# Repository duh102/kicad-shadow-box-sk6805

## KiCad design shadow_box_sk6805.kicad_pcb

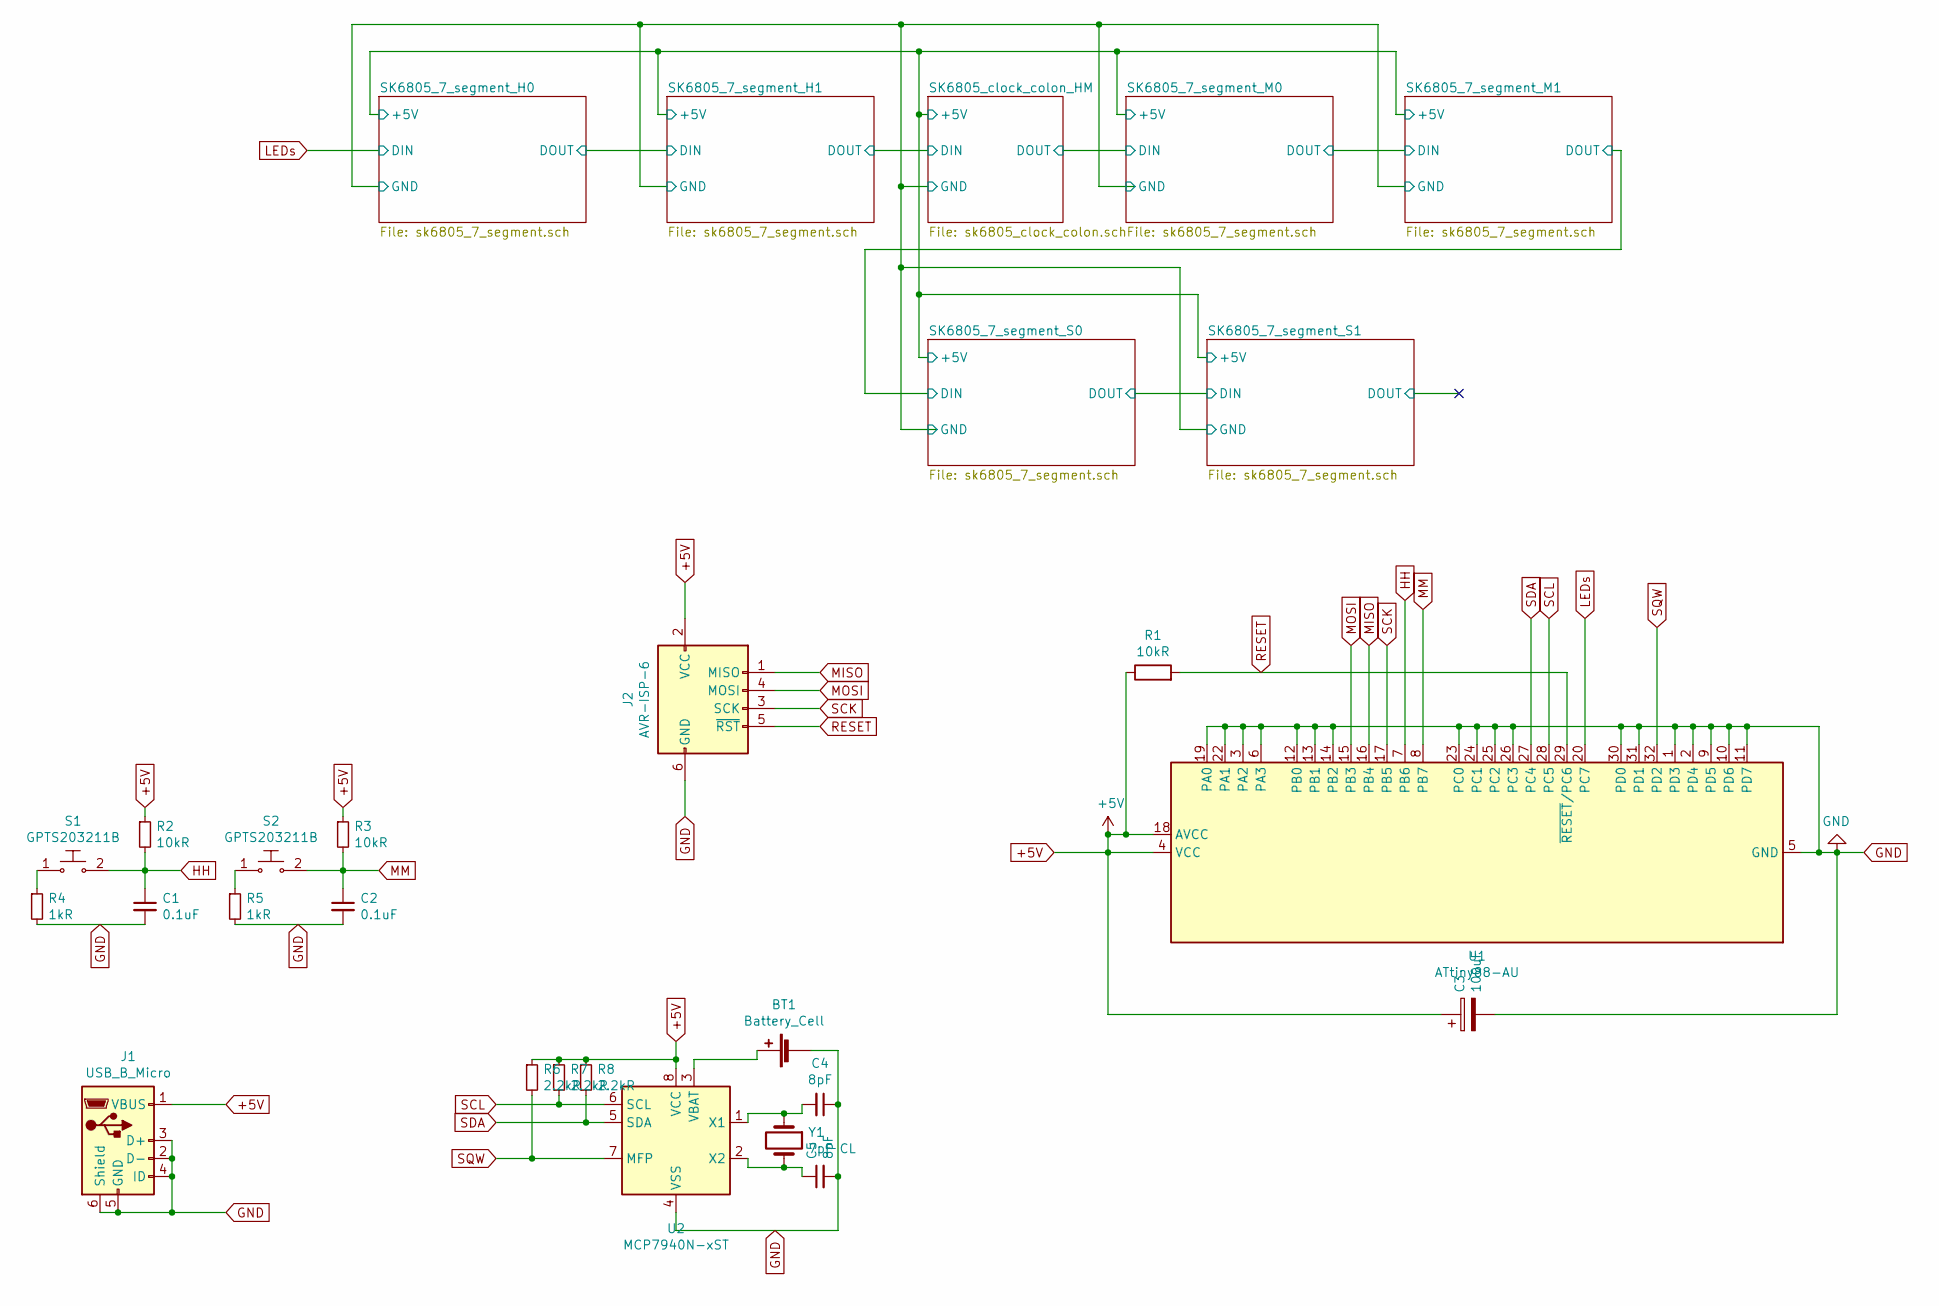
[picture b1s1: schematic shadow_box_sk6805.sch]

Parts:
BT1: Battery_Cell; BatteryHolder_Keystone_3034_1x20mm
C1, C2: 0.1uF; C_0805_2012Metric
C3: 100uF; CP_Radial_D6.3mm_P2.50mm
C4, C5: 8pF; C_0805_2012Metric
J1: USB_B_Micro; USB_Micro_B_Female_10118194-0001LF
J2: AVR-ISP-6; PinHeader_2x03_P2.54mm_Vertical_SMD
R1, R2, R3: 10kR; R_0805_2012Metric
R4, R5: 1kR; R_0805_2012Metric
R6, R7, R8: 2.2kR; R_0805_2012Metric
S1, S2: GPTS203211B; SW_SPST_FSMSM; MPN GPTS203211B; Digi-Key_PN CW181-ND
U1: ATtiny88-AU; TQFP-32_7x7mm_P0.8mm
U2: MCP7940N-xST; SOIC-8_3.9x4.9mm_P1.27mm
Y1: 7pF CL; Crystal_SMD_3215-2Pin_3.2x1.5mm

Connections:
+5V: C3.1, J1.1 (VBUS), J2.2 (VCC), R1.1, R2.1, R3.1, R6.1, R7.1, R8.1, U1.4 (VCC), U1.18 (AVCC), U2.8 (VCC); also elsewhere on the board
GND: BT1.2 (-), C1.2, C2.2, C3.2, C4.1, C5.2, J1.2 (D-), J1.3 (D+), J1.4 (ID), J1.5 (GND), J1.6 (Shield), J2.6 (GND), R4.2, R5.2, U1.1 (PD3), U1.2 (PD4), U1.3 (PA2), U1.5 (GND), U1.6 (PA3), U1.9 (PD5), U1.10 (PD6), U1.11 (PD7), U1.12 (PB0), U1.13 (PB1), U1.14 (PB2), U1.19 (PA0), U1.21 (GND), U1.22 (PA1), U1.23 (PC0), U1.24 (PC1), U1.25 (PC2), U1.26 (PC3), U1.30 (PD0), U1.31 (PD1), U2.4 (VSS); also elsewhere on the board
HH: C1.1, R2.2, S1.2, U1.7 (PB6)
LEDs: U1.20 (PC7); also elsewhere on the board
MISO: J2.1 (MISO), U1.16 (PB4)
MM: C2.1, R3.2, S2.2, U1.8 (PB7)
MOSI: J2.4 (MOSI), U1.15 (PB3)
unnamed: BT1.1 (+), U2.3 (VBAT)
unnamed: C4.2, U2.1 (X1), Y1.1
unnamed: C5.1, U2.2 (X2), Y1.2
unnamed: R4.1, S1.1
unnamed: R5.1, S2.1
RESET: J2.5 (~RST), R1.2, U1.29 (~RESET~/PC6)
SCK: J2.3 (SCK), U1.17 (PB5)
SCL: R7.2, U1.28 (PC5), U2.6 (SCL)
SDA: R8.2, U1.27 (PC4), U2.5 (SDA)
SQW: R6.2, U1.32 (PD2), U2.7 (MFP)

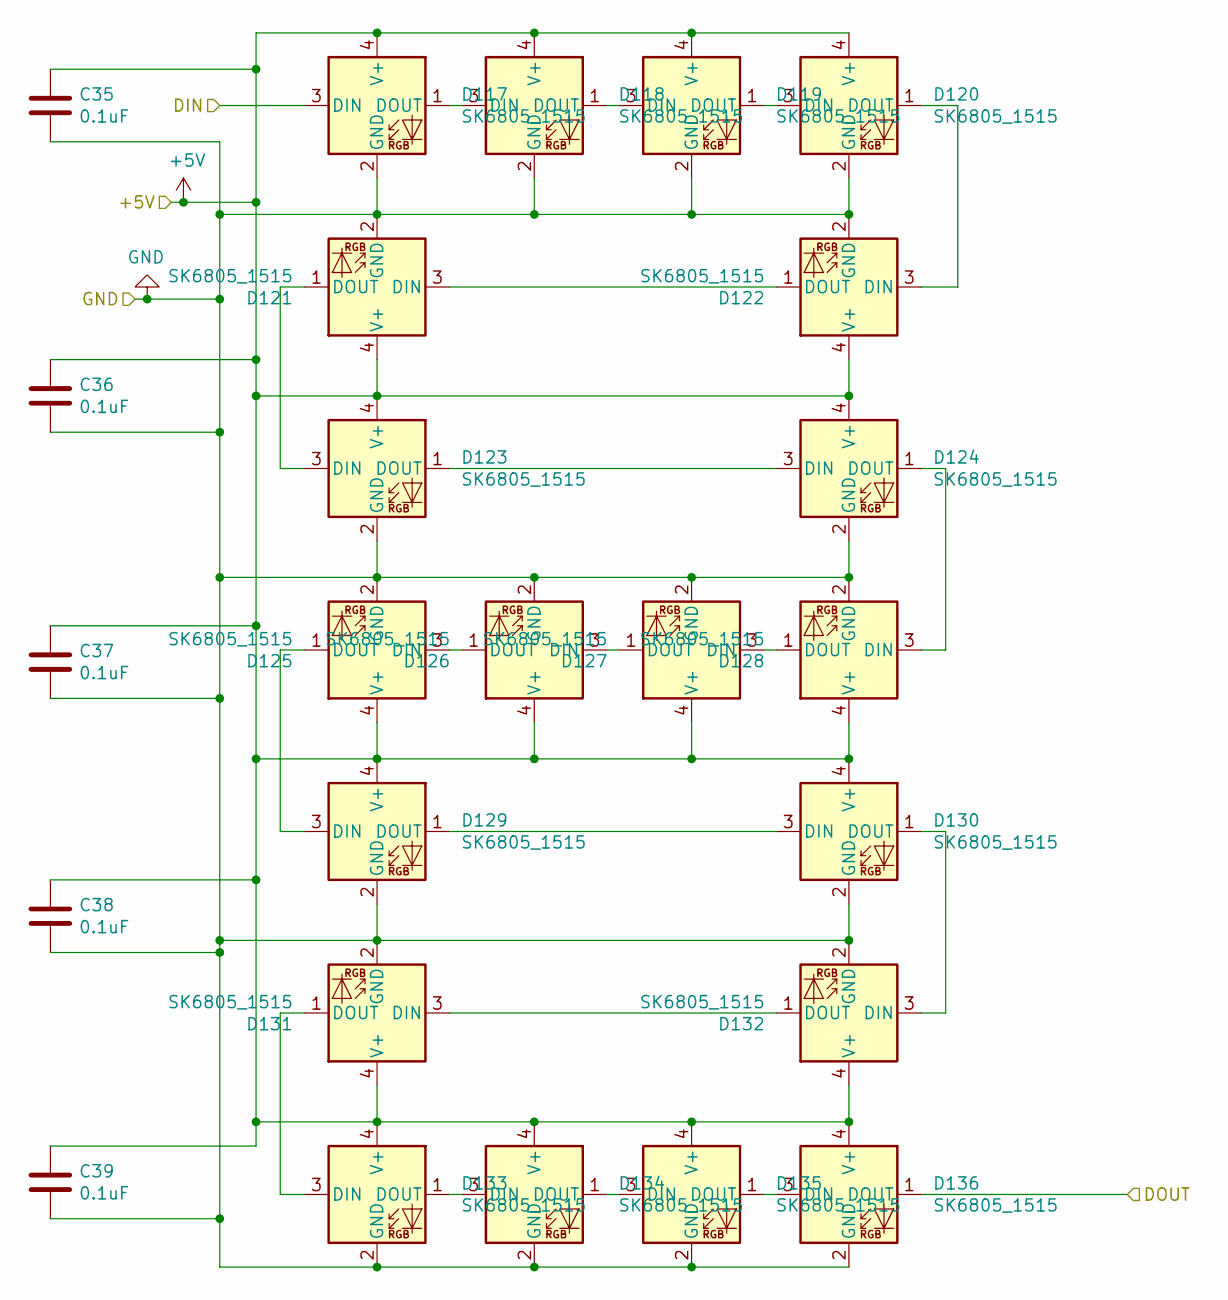
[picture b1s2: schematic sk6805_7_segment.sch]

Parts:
C35, C36, C37, C38, C39: 0.1uF; C_0805_2012Metric
D117, D118, D119, D120, D121, D122, D123, D124, D125, D126, D127, D128, D129, D130, D131, D132, D133, D134, D135, D136: SK6805_1515; LED_SK6805_PLCC4_1.5x1.5mm_P0.65mm

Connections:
+5V: C35.1, C36.1, C37.1, C38.1, C39.1, D117.4 (V+), D118.4 (V+), D119.4 (V+), D120.4 (V+), D121.4 (V+), D122.4 (V+), D123.4 (V+), D124.4 (V+), D125.4 (V+), D126.4 (V+), D127.4 (V+), D128.4 (V+), D129.4 (V+), D130.4 (V+), D131.4 (V+), D132.4 (V+), D133.4 (V+), D134.4 (V+), D135.4 (V+), D136.4 (V+); also elsewhere on the board
/SK6805_7_segment_H1/DIN: D136.1 (DOUT); also elsewhere on the board
GND: C35.2, C36.2, C37.2, C38.2, C39.2, D117.2 (GND), D118.2 (GND), D119.2 (GND), D120.2 (GND), D121.2 (GND), D122.2 (GND), D123.2 (GND), D124.2 (GND), D125.2 (GND), D126.2 (GND), D127.2 (GND), D128.2 (GND), D129.2 (GND), D130.2 (GND), D131.2 (GND), D132.2 (GND), D133.2 (GND), D134.2 (GND), D135.2 (GND), D136.2 (GND); also elsewhere on the board
LEDs: D117.3 (DIN); also elsewhere on the board
unnamed: D117.1 (DOUT), D118.3 (DIN)
unnamed: D118.1 (DOUT), D119.3 (DIN)
unnamed: D119.1 (DOUT), D120.3 (DIN)
unnamed: D120.1 (DOUT), D122.3 (DIN)
unnamed: D121.1 (DOUT), D123.3 (DIN)
unnamed: D121.3 (DIN), D122.1 (DOUT)
unnamed: D123.1 (DOUT), D124.3 (DIN)
unnamed: D124.1 (DOUT), D128.3 (DIN)
unnamed: D125.1 (DOUT), D129.3 (DIN)
unnamed: D125.3 (DIN), D126.1 (DOUT)
unnamed: D126.3 (DIN), D127.1 (DOUT)
unnamed: D127.3 (DIN), D128.1 (DOUT)
unnamed: D129.1 (DOUT), D130.3 (DIN)
unnamed: D130.1 (DOUT), D132.3 (DIN)
unnamed: D131.1 (DOUT), D133.3 (DIN)
unnamed: D131.3 (DIN), D132.1 (DOUT)
unnamed: D133.1 (DOUT), D134.3 (DIN)
unnamed: D134.1 (DOUT), D135.3 (DIN)
unnamed: D135.1 (DOUT), D136.3 (DIN)

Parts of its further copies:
C6, C7, C8, C9, C10, C11, C12, C13, C14, C15, C20, C21, C22, C23, C24, C25, C26, C27, C28, C29, C30, C31, C32, C33, C34: 0.1uF; C_0805_2012Metric
D1, D2, D3, D4, D5, D6, D7, D8, D9, D10, D11, D12, D13, D14, D15, D16, D17, D18, D19, D20, D21, D22, D23, D24, D25, D26, D27, D28, D29, D30, D31, D32, D33, D34, D35, D36, D37, D38, D39, D40, D57, D58, D59, D60, D61, D62, D63, D64, D65, D66, D67, D68, D69, D70, D71, D72, D73, D74, D75, D76, D77, D78, D79, D80, D81, D82, D83, D84, D85, D86, D87, D88, D89, D90, D91, D92, D93, D94, D95, D96, D97, D98, D99, D100, D101, D102, D103, D104, D105, D106, D107, D108, D109, D110, D111, D112, D113, D114, D115, D116: SK6805_1515; LED_SK6805_PLCC4_1.5x1.5mm_P0.65mm

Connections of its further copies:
+5V: C6.1, C7.1, C8.1, C9.1, C10.1, C11.1, C12.1, C13.1, C14.1, C15.1, C20.1, C21.1, C22.1, C23.1, C24.1, C25.1, C26.1, C27.1, C28.1, C29.1, C30.1, C31.1, C32.1, C33.1, C34.1, D1.4 (V+), D2.4 (V+), D3.4 (V+), D4.4 (V+), D5.4 (V+), D6.4 (V+), D7.4 (V+), D8.4 (V+), D9.4 (V+), D10.4 (V+), D11.4 (V+), D12.4 (V+), D13.4 (V+), D14.4 (V+), D15.4 (V+), D16.4 (V+), D17.4 (V+), D18.4 (V+), D19.4 (V+), D20.4 (V+), D21.4 (V+), D22.4 (V+), D23.4 (V+), D24.4 (V+), D25.4 (V+), D26.4 (V+), D27.4 (V+), D28.4 (V+), D29.4 (V+), D30.4 (V+), D31.4 (V+), D32.4 (V+), D33.4 (V+), D34.4 (V+), D35.4 (V+), D36.4 (V+), D37.4 (V+), D38.4 (V+), D39.4 (V+), D40.4 (V+), D57.4 (V+), D58.4 (V+), D59.4 (V+), D60.4 (V+), D61.4 (V+), D62.4 (V+), D63.4 (V+), D64.4 (V+), D65.4 (V+), D66.4 (V+), D67.4 (V+), D68.4 (V+), D69.4 (V+), D70.4 (V+), D71.4 (V+), D72.4 (V+), D73.4 (V+), D74.4 (V+), D75.4 (V+), D76.4 (V+), D77.4 (V+), D78.4 (V+), D79.4 (V+), D80.4 (V+), D81.4 (V+), D82.4 (V+), D83.4 (V+), D84.4 (V+), D85.4 (V+), D86.4 (V+), D87.4 (V+), D88.4 (V+), D89.4 (V+), D90.4 (V+), D91.4 (V+), D92.4 (V+), D93.4 (V+), D94.4 (V+), D95.4 (V+), D96.4 (V+), D97.4 (V+), D98.4 (V+), D99.4 (V+), D100.4 (V+), D101.4 (V+), D102.4 (V+), D103.4 (V+), D104.4 (V+), D105.4 (V+), D106.4 (V+), D107.4 (V+), D108.4 (V+), D109.4 (V+), D110.4 (V+), D111.4 (V+), D112.4 (V+), D113.4 (V+), D114.4 (V+), D115.4 (V+), D116.4 (V+); also elsewhere on the board
/SK6805_7_segment_H1/DIN: D97.3 (DIN); also elsewhere on the board
/SK6805_7_segment_M0/DIN: D77.3 (DIN); also elsewhere on the board
/SK6805_7_segment_M1/DIN: D57.3 (DIN), D96.1 (DOUT)
/SK6805_7_segment_S0/DIN: D1.3 (DIN), D76.1 (DOUT)
/SK6805_7_segment_S1/DIN: D20.1 (DOUT), D21.3 (DIN)
/SK6805_clock_colon_HM/DIN: D116.1 (DOUT); also elsewhere on the board
GND: C6.2, C7.2, C8.2, C9.2, C10.2, C11.2, C12.2, C13.2, C14.2, C15.2, C20.2, C21.2, C22.2, C23.2, C24.2, C25.2, C26.2, C27.2, C28.2, C29.2, C30.2, C31.2, C32.2, C33.2, C34.2, D1.2 (GND), D2.2 (GND), D3.2 (GND), D4.2 (GND), D5.2 (GND), D6.2 (GND), D7.2 (GND), D8.2 (GND), D9.2 (GND), D10.2 (GND), D11.2 (GND), D12.2 (GND), D13.2 (GND), D14.2 (GND), D15.2 (GND), D16.2 (GND), D17.2 (GND), D18.2 (GND), D19.2 (GND), D20.2 (GND), D21.2 (GND), D22.2 (GND), D23.2 (GND), D24.2 (GND), D25.2 (GND), D26.2 (GND), D27.2 (GND), D28.2 (GND), D29.2 (GND), D30.2 (GND), D31.2 (GND), D32.2 (GND), D33.2 (GND), D34.2 (GND), D35.2 (GND), D36.2 (GND), D37.2 (GND), D38.2 (GND), D39.2 (GND), D40.2 (GND), D57.2 (GND), D58.2 (GND), D59.2 (GND), D60.2 (GND), D61.2 (GND), D62.2 (GND), D63.2 (GND), D64.2 (GND), D65.2 (GND), D66.2 (GND), D67.2 (GND), D68.2 (GND), D69.2 (GND), D70.2 (GND), D71.2 (GND), D72.2 (GND), D73.2 (GND), D74.2 (GND), D75.2 (GND), D76.2 (GND), D77.2 (GND), D78.2 (GND), D79.2 (GND), D80.2 (GND), D81.2 (GND), D82.2 (GND), D83.2 (GND), D84.2 (GND), D85.2 (GND), D86.2 (GND), D87.2 (GND), D88.2 (GND), D89.2 (GND), D90.2 (GND), D91.2 (GND), D92.2 (GND), D93.2 (GND), D94.2 (GND), D95.2 (GND), D96.2 (GND), D97.2 (GND), D98.2 (GND), D99.2 (GND), D100.2 (GND), D101.2 (GND), D102.2 (GND), D103.2 (GND), D104.2 (GND), D105.2 (GND), D106.2 (GND), D107.2 (GND), D108.2 (GND), D109.2 (GND), D110.2 (GND), D111.2 (GND), D112.2 (GND), D113.2 (GND), D114.2 (GND), D115.2 (GND), D116.2 (GND); also elsewhere on the board
unnamed: D1.1 (DOUT), D2.3 (DIN)
unnamed: D2.1 (DOUT), D3.3 (DIN)
unnamed: D3.1 (DOUT), D4.3 (DIN)
unnamed: D4.1 (DOUT), D6.3 (DIN)
unnamed: D5.1 (DOUT), D7.3 (DIN)
unnamed: D5.3 (DIN), D6.1 (DOUT)
unnamed: D7.1 (DOUT), D8.3 (DIN)
unnamed: D9.3 (DIN), D10.1 (DOUT)
unnamed: D10.3 (DIN), D11.1 (DOUT)
unnamed: D11.3 (DIN), D12.1 (DOUT)
unnamed: D8.1 (DOUT), D12.3 (DIN)
unnamed: D13.1 (DOUT), D14.3 (DIN)
unnamed: D9.1 (DOUT), D13.3 (DIN)
unnamed: D14.1 (DOUT), D16.3 (DIN)
unnamed: D15.1 (DOUT), D17.3 (DIN)
unnamed: D15.3 (DIN), D16.1 (DOUT)
unnamed: D17.1 (DOUT), D18.3 (DIN)
unnamed: D18.1 (DOUT), D19.3 (DIN)
unnamed: D19.1 (DOUT), D20.3 (DIN)
unnamed: D21.1 (DOUT), D22.3 (DIN)
unnamed: D22.1 (DOUT), D23.3 (DIN)
unnamed: D23.1 (DOUT), D24.3 (DIN)
unnamed: D24.1 (DOUT), D26.3 (DIN)
unnamed: D25.1 (DOUT), D27.3 (DIN)
unnamed: D25.3 (DIN), D26.1 (DOUT)
unnamed: D27.1 (DOUT), D28.3 (DIN)
unnamed: D28.1 (DOUT), D32.3 (DIN)
unnamed: D29.1 (DOUT), D33.3 (DIN)
unnamed: D29.3 (DIN), D30.1 (DOUT)
unnamed: D30.3 (DIN), D31.1 (DOUT)
unnamed: D31.3 (DIN), D32.1 (DOUT)
unnamed: D33.1 (DOUT), D34.3 (DIN)
unnamed: D34.1 (DOUT), D36.3 (DIN)
unnamed: D35.1 (DOUT), D37.3 (DIN)
unnamed: D35.3 (DIN), D36.1 (DOUT)
unnamed: D37.1 (DOUT), D38.3 (DIN)
unnamed: D38.1 (DOUT), D39.3 (DIN)
unnamed: D39.1 (DOUT), D40.3 (DIN)
unnamed: D57.1 (DOUT), D58.3 (DIN)
unnamed: D58.1 (DOUT), D59.3 (DIN)
unnamed: D59.1 (DOUT), D60.3 (DIN)
unnamed: D60.1 (DOUT), D62.3 (DIN)
unnamed: D61.1 (DOUT), D63.3 (DIN)
unnamed: D61.3 (DIN), D62.1 (DOUT)
unnamed: D63.1 (DOUT), D64.3 (DIN)
unnamed: D64.1 (DOUT), D68.3 (DIN)
unnamed: D65.1 (DOUT), D69.3 (DIN)
unnamed: D65.3 (DIN), D66.1 (DOUT)
unnamed: D66.3 (DIN), D67.1 (DOUT)
unnamed: D67.3 (DIN), D68.1 (DOUT)
unnamed: D69.1 (DOUT), D70.3 (DIN)
unnamed: D70.1 (DOUT), D72.3 (DIN)
unnamed: D71.1 (DOUT), D73.3 (DIN)
unnamed: D71.3 (DIN), D72.1 (DOUT)
unnamed: D73.1 (DOUT), D74.3 (DIN)
unnamed: D74.1 (DOUT), D75.3 (DIN)
unnamed: D75.1 (DOUT), D76.3 (DIN)
unnamed: D77.1 (DOUT), D78.3 (DIN)
unnamed: D78.1 (DOUT), D79.3 (DIN)
unnamed: D79.1 (DOUT), D80.3 (DIN)
unnamed: D80.1 (DOUT), D82.3 (DIN)
unnamed: D81.1 (DOUT), D83.3 (DIN)
unnamed: D81.3 (DIN), D82.1 (DOUT)
unnamed: D83.1 (DOUT), D84.3 (DIN)
unnamed: D84.1 (DOUT), D88.3 (DIN)
unnamed: D85.1 (DOUT), D89.3 (DIN)
unnamed: D85.3 (DIN), D86.1 (DOUT)
unnamed: D86.3 (DIN), D87.1 (DOUT)
unnamed: D87.3 (DIN), D88.1 (DOUT)
unnamed: D89.1 (DOUT), D90.3 (DIN)
unnamed: D90.1 (DOUT), D92.3 (DIN)
unnamed: D91.1 (DOUT), D93.3 (DIN)
unnamed: D91.3 (DIN), D92.1 (DOUT)
unnamed: D93.1 (DOUT), D94.3 (DIN)
unnamed: D94.1 (DOUT), D95.3 (DIN)
unnamed: D95.1 (DOUT), D96.3 (DIN)
unnamed: D97.1 (DOUT), D98.3 (DIN)
unnamed: D98.1 (DOUT), D99.3 (DIN)
unnamed: D100.1 (DOUT), D102.3 (DIN)
unnamed: D99.1 (DOUT), D100.3 (DIN)
unnamed: D101.1 (DOUT), D103.3 (DIN)
unnamed: D101.3 (DIN), D102.1 (DOUT)
unnamed: D103.1 (DOUT), D104.3 (DIN)
unnamed: D104.1 (DOUT), D108.3 (DIN)
unnamed: D105.1 (DOUT), D109.3 (DIN)
unnamed: D105.3 (DIN), D106.1 (DOUT)
unnamed: D106.3 (DIN), D107.1 (DOUT)
unnamed: D107.3 (DIN), D108.1 (DOUT)
unnamed: D109.1 (DOUT), D110.3 (DIN)
unnamed: D110.1 (DOUT), D112.3 (DIN)
unnamed: D111.1 (DOUT), D113.3 (DIN)
unnamed: D111.3 (DIN), D112.1 (DOUT)
unnamed: D113.1 (DOUT), D114.3 (DIN)
unnamed: D114.1 (DOUT), D115.3 (DIN)
unnamed: D115.1 (DOUT), D116.3 (DIN)

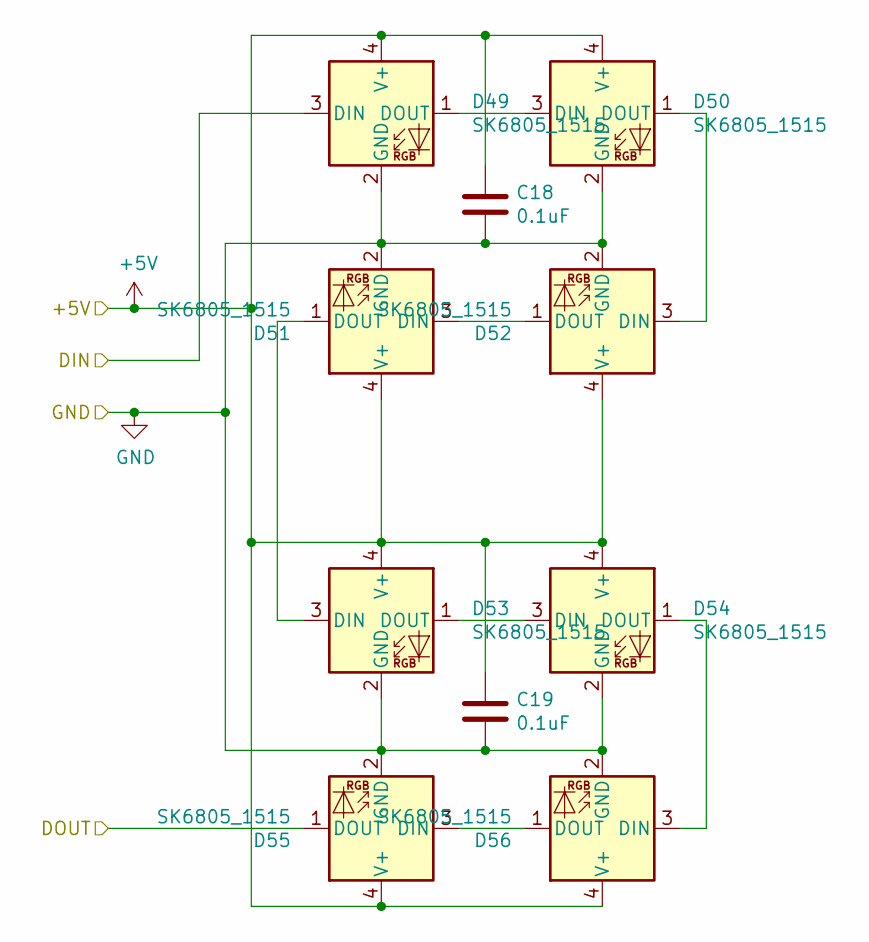
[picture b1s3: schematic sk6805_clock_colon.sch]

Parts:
C18, C19: 0.1uF; C_0805_2012Metric
D49, D50, D51, D52, D53, D54, D55, D56: SK6805_1515; LED_SK6805_PLCC4_1.5x1.5mm_P0.65mm

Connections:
+5V: C18.1, C19.1, D49.4 (V+), D50.4 (V+), D51.4 (V+), D52.4 (V+), D53.4 (V+), D54.4 (V+), D55.4 (V+), D56.4 (V+); also elsewhere on the board
/SK6805_7_segment_M0/DIN: D55.1 (DOUT); also elsewhere on the board
/SK6805_clock_colon_HM/DIN: D49.3 (DIN); also elsewhere on the board
GND: C18.2, C19.2, D49.2 (GND), D50.2 (GND), D51.2 (GND), D52.2 (GND), D53.2 (GND), D54.2 (GND), D55.2 (GND), D56.2 (GND); also elsewhere on the board
unnamed: D49.1 (DOUT), D50.3 (DIN)
unnamed: D50.1 (DOUT), D52.3 (DIN)
unnamed: D51.1 (DOUT), D53.3 (DIN)
unnamed: D51.3 (DIN), D52.1 (DOUT)
unnamed: D53.1 (DOUT), D54.3 (DIN)
unnamed: D54.1 (DOUT), D56.3 (DIN)
unnamed: D55.3 (DIN), D56.1 (DOUT)

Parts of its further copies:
C16, C17: 0.1uF; C_0805_2012Metric
D41, D42, D43, D44, D45, D46, D47, D48: SK6805_1515; LED_SK6805_PLCC4_1.5x1.5mm_P0.65mm

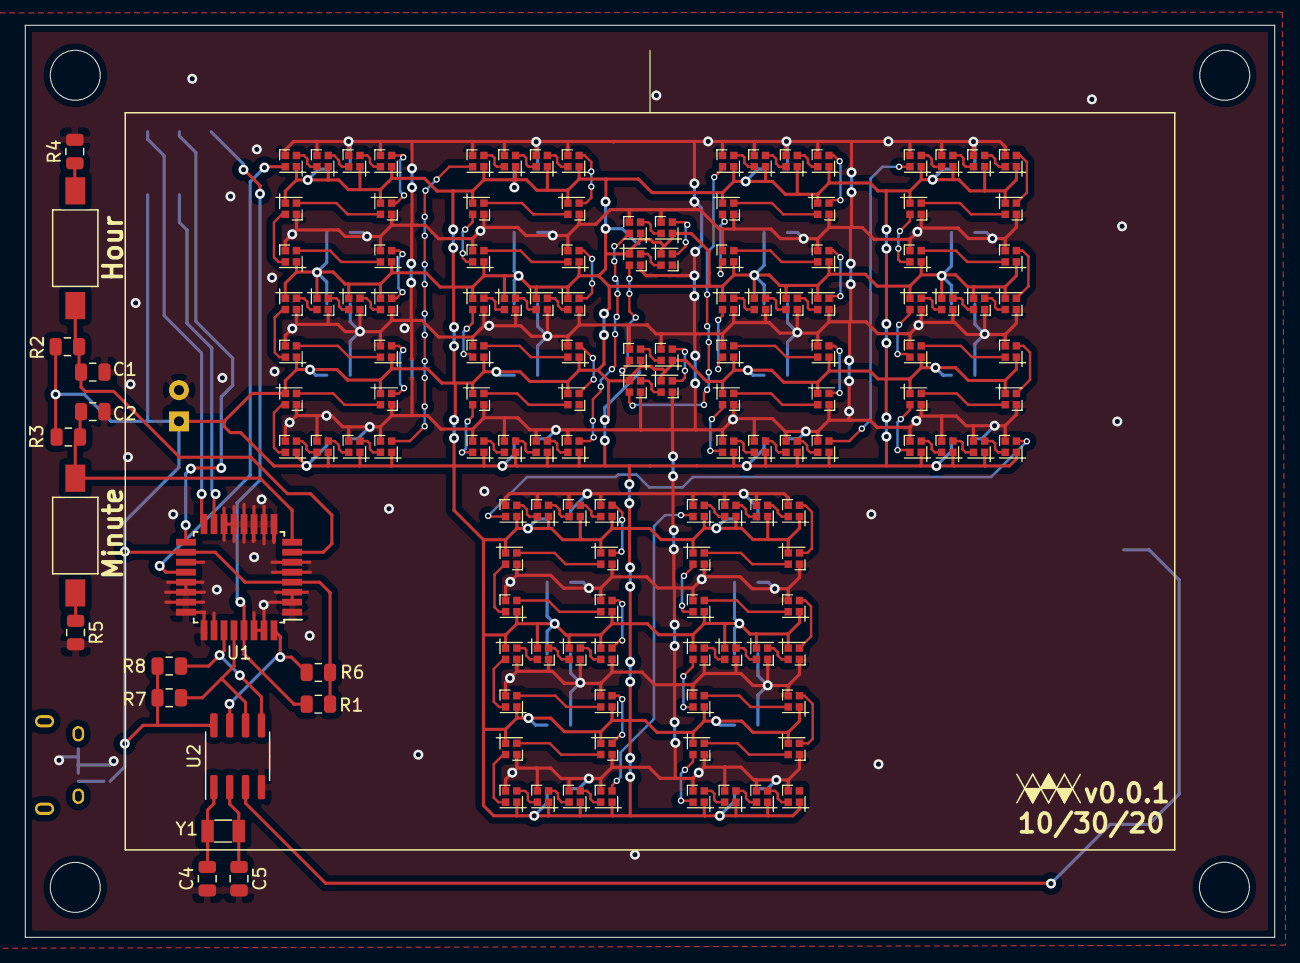
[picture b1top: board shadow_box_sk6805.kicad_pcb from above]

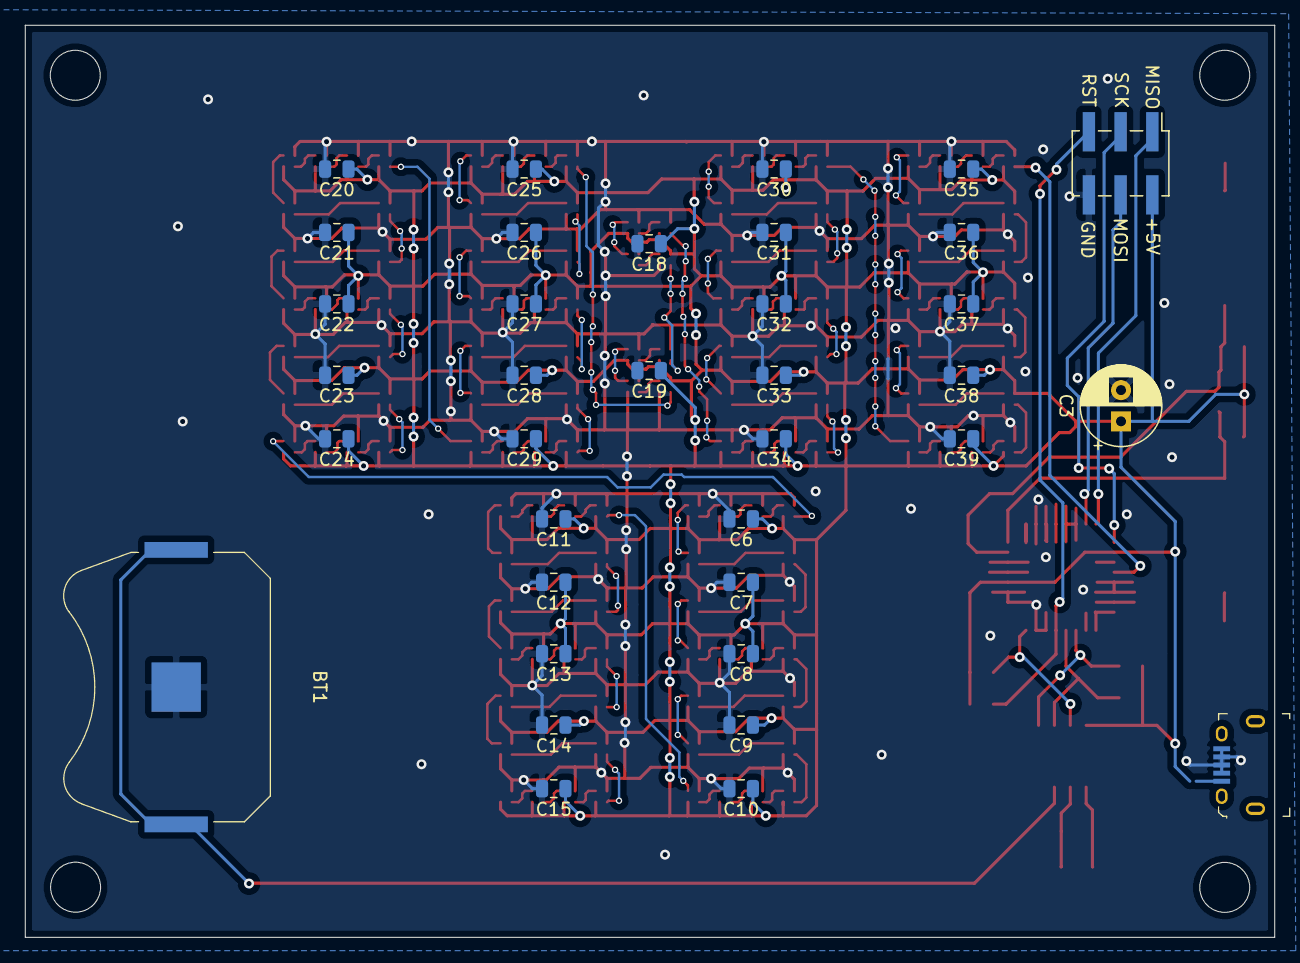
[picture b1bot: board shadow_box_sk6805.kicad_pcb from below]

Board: 2 copper layers, 100.0 x 73.0 mm, 181 parts (36 on the bottom side), 144 nets.

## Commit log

2020-04-13 Initial commit; board laid out
2020-04-13 Add ISP header, wire up everything
2020-04-16 Optimize ground plane a bit; output gbr
2020-10-30 Update usb position, byline
